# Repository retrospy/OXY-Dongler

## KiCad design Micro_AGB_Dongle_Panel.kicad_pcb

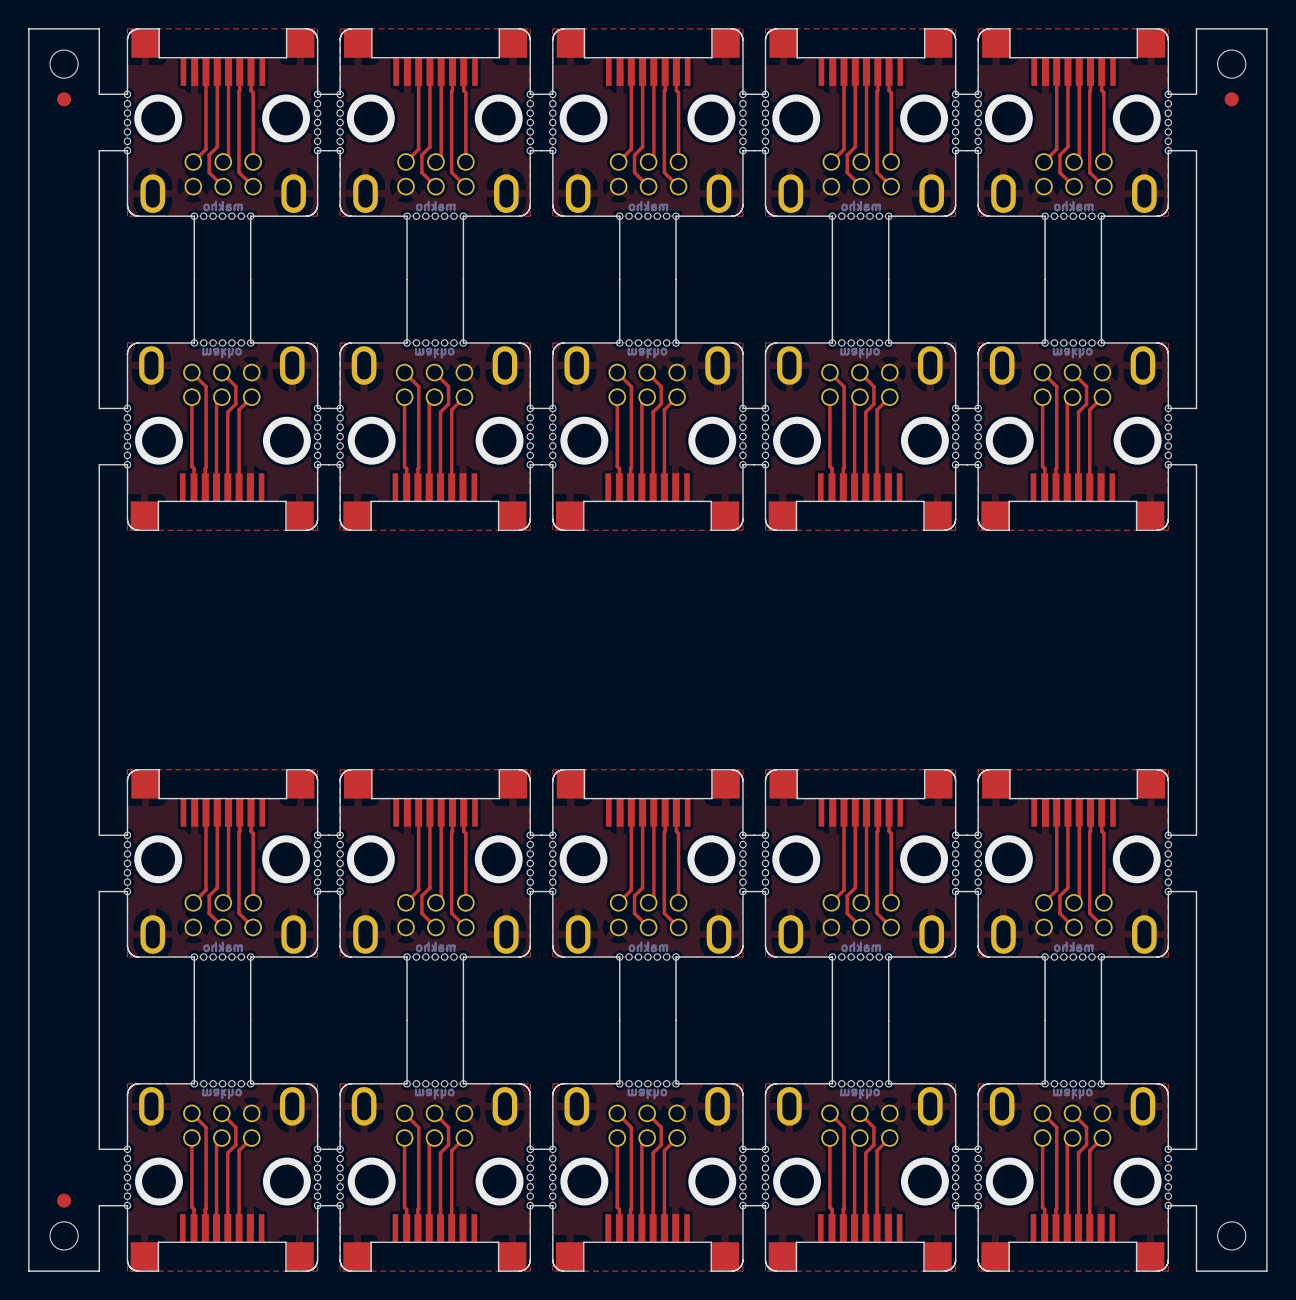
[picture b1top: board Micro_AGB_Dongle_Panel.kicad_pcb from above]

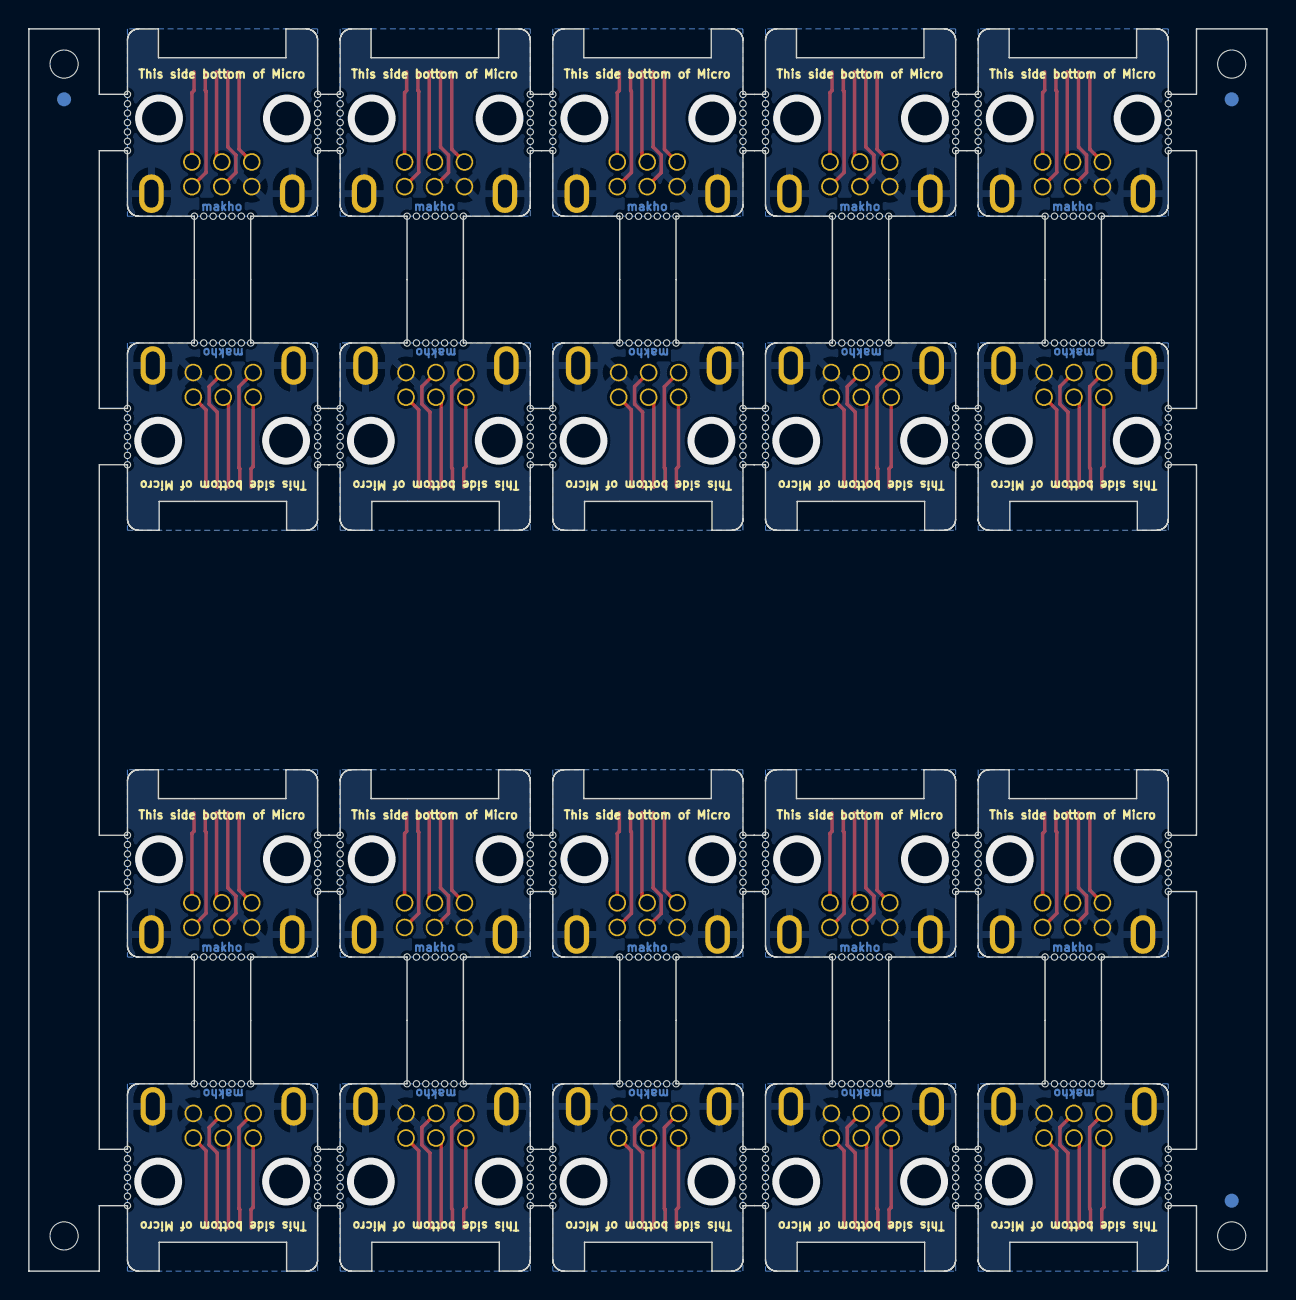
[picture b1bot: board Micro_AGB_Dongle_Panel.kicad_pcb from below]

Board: 2 copper layers, 87.9 x 88.2 mm, 470 parts (3 on the bottom side), 120 nets.

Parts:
EXP1, EXP1#2, EXP1#3, EXP1#4, EXP1#5, EXP1#6, EXP1#7, EXP1#8, EXP1#9, EXP1#10, EXP1#11, EXP1#12, EXP1#13, EXP1#14, EXP1#15, EXP1#16, EXP1#17, EXP1#18, EXP1#19, EXP1#20: OXY_EXP
EXP2, EXP2#2, EXP2#3, EXP2#4, EXP2#5, EXP2#6, EXP2#7, EXP2#8, EXP2#9, EXP2#10, EXP2#11, EXP2#12, EXP2#13, EXP2#14, EXP2#15, EXP2#16, EXP2#17, EXP2#18, EXP2#19, EXP2#20: AGB_EXP
KiKit_FID_B_1, KiKit_FID_B_2, KiKit_FID_B_3: Fiducial
KiKit_FID_T_1, KiKit_FID_T_2, KiKit_FID_T_3: Fiducial
KiKit_MB_1_1, KiKit_MB_1_2, KiKit_MB_1_3, KiKit_MB_1_4, KiKit_MB_1_5, KiKit_MB_1_6, KiKit_MB_1_7, KiKit_MB_2_1, KiKit_MB_2_2, KiKit_MB_2_3, KiKit_MB_2_4, KiKit_MB_2_5, KiKit_MB_2_6, KiKit_MB_2_7, KiKit_MB_3_1, KiKit_MB_3_2, KiKit_MB_3_3, KiKit_MB_3_4, KiKit_MB_3_5, KiKit_MB_3_6, KiKit_MB_3_7, KiKit_MB_4_1, KiKit_MB_4_2, KiKit_MB_4_3, KiKit_MB_4_4, KiKit_MB_4_5, KiKit_MB_4_6, KiKit_MB_4_7, KiKit_MB_5_1, KiKit_MB_5_2, KiKit_MB_5_3, KiKit_MB_5_4, KiKit_MB_5_5, KiKit_MB_5_6, KiKit_MB_5_7, KiKit_MB_6_1, KiKit_MB_6_2, KiKit_MB_6_3, KiKit_MB_6_4, KiKit_MB_6_5, KiKit_MB_6_6, KiKit_MB_6_7, KiKit_MB_7_1, KiKit_MB_7_2, KiKit_MB_7_3, KiKit_MB_7_4, KiKit_MB_7_5, KiKit_MB_7_6, KiKit_MB_7_7, KiKit_MB_8_1, KiKit_MB_8_2, KiKit_MB_8_3, KiKit_MB_8_4, KiKit_MB_8_5, KiKit_MB_8_6, KiKit_MB_8_7, KiKit_MB_9_1, KiKit_MB_9_2, KiKit_MB_9_3, KiKit_MB_9_4, KiKit_MB_9_5, KiKit_MB_9_6, KiKit_MB_9_7, KiKit_MB_10_1, KiKit_MB_10_2, KiKit_MB_10_3, KiKit_MB_10_4, KiKit_MB_10_5, KiKit_MB_10_6, KiKit_MB_10_7, KiKit_MB_11_1, KiKit_MB_11_2, KiKit_MB_11_3, KiKit_MB_11_4, KiKit_MB_11_5, KiKit_MB_11_6, KiKit_MB_11_7, KiKit_MB_12_1, KiKit_MB_12_2, KiKit_MB_12_3, KiKit_MB_12_4, KiKit_MB_12_5, KiKit_MB_12_6, KiKit_MB_12_7, KiKit_MB_13_1, KiKit_MB_13_2, KiKit_MB_13_3, KiKit_MB_13_4, KiKit_MB_13_5, KiKit_MB_13_6, KiKit_MB_13_7, KiKit_MB_14_1, KiKit_MB_14_2, KiKit_MB_14_3, KiKit_MB_14_4, KiKit_MB_14_5, KiKit_MB_14_6, KiKit_MB_14_7, KiKit_MB_15_1, KiKit_MB_15_2, KiKit_MB_15_3, KiKit_MB_15_4, KiKit_MB_15_5, KiKit_MB_15_6, KiKit_MB_15_7, KiKit_MB_16_1, KiKit_MB_16_2, KiKit_MB_16_3, KiKit_MB_16_4, KiKit_MB_16_5, KiKit_MB_16_6, KiKit_MB_16_7, KiKit_MB_17_1, KiKit_MB_17_2, KiKit_MB_17_3, KiKit_MB_17_4, KiKit_MB_17_5, KiKit_MB_17_6, KiKit_MB_17_7, KiKit_MB_18_1, KiKit_MB_18_2, KiKit_MB_18_3, KiKit_MB_18_4, KiKit_MB_18_5, KiKit_MB_18_6, KiKit_MB_18_7, KiKit_MB_20_1, KiKit_MB_20_2, KiKit_MB_20_3, KiKit_MB_20_4, KiKit_MB_20_5, KiKit_MB_20_6, KiKit_MB_20_7, KiKit_MB_21_1, KiKit_MB_21_2, KiKit_MB_21_3, KiKit_MB_21_4, KiKit_MB_21_5, KiKit_MB_21_6, KiKit_MB_21_7, KiKit_MB_22_1, KiKit_MB_22_2, KiKit_MB_22_3, KiKit_MB_22_4, KiKit_MB_22_5, KiKit_MB_22_6, KiKit_MB_22_7, KiKit_MB_24_1, KiKit_MB_24_2, KiKit_MB_24_3, KiKit_MB_24_4, KiKit_MB_24_5, KiKit_MB_24_6, KiKit_MB_24_7, KiKit_MB_25_1, KiKit_MB_25_2, KiKit_MB_25_3, KiKit_MB_25_4, KiKit_MB_25_5, KiKit_MB_25_6, KiKit_MB_25_7, KiKit_MB_26_1, KiKit_MB_26_2, KiKit_MB_26_3, KiKit_MB_26_4, KiKit_MB_26_5, KiKit_MB_26_6, KiKit_MB_26_7, KiKit_MB_28_1, KiKit_MB_28_2, KiKit_MB_28_3, KiKit_MB_28_4, KiKit_MB_28_5, KiKit_MB_28_6, KiKit_MB_28_7, KiKit_MB_29_1, KiKit_MB_29_2, KiKit_MB_29_3, KiKit_MB_29_4, KiKit_MB_29_5, KiKit_MB_29_6, KiKit_MB_29_7, KiKit_MB_30_1, KiKit_MB_30_2, KiKit_MB_30_3, KiKit_MB_30_4, KiKit_MB_30_5, KiKit_MB_30_6, KiKit_MB_30_7, KiKit_MB_32_1, KiKit_MB_32_2, KiKit_MB_32_3, KiKit_MB_32_4, KiKit_MB_32_5, KiKit_MB_32_6, KiKit_MB_32_7, KiKit_MB_33_1, KiKit_MB_33_2, KiKit_MB_33_3, KiKit_MB_33_4, KiKit_MB_33_5, KiKit_MB_33_6, KiKit_MB_33_7, KiKit_MB_34_1, KiKit_MB_34_2, KiKit_MB_34_3, KiKit_MB_34_4, KiKit_MB_34_5, KiKit_MB_34_6, KiKit_MB_34_7, KiKit_MB_36_1, KiKit_MB_36_2, KiKit_MB_36_3, KiKit_MB_36_4, KiKit_MB_36_5, KiKit_MB_36_6, KiKit_MB_36_7, KiKit_MB_37_1, KiKit_MB_37_2, KiKit_MB_37_3, KiKit_MB_37_4, KiKit_MB_37_5, KiKit_MB_37_6, KiKit_MB_37_7, KiKit_MB_39_1, KiKit_MB_39_2, KiKit_MB_39_3, KiKit_MB_39_4, KiKit_MB_39_5, KiKit_MB_39_6, KiKit_MB_39_7, KiKit_MB_40_1, KiKit_MB_40_2, KiKit_MB_40_3, KiKit_MB_40_4, KiKit_MB_40_5, KiKit_MB_40_6, KiKit_MB_40_7, KiKit_MB_41_1, KiKit_MB_41_2, KiKit_MB_41_3, KiKit_MB_41_4, KiKit_MB_41_5, KiKit_MB_41_6, KiKit_MB_41_7, KiKit_MB_43_1, KiKit_MB_43_2, KiKit_MB_43_3, KiKit_MB_43_4, KiKit_MB_43_5, KiKit_MB_43_6, KiKit_MB_43_7, KiKit_MB_44_1, KiKit_MB_44_2, KiKit_MB_44_3, KiKit_MB_44_4, KiKit_MB_44_5, KiKit_MB_44_6, KiKit_MB_44_7, KiKit_MB_45_1, KiKit_MB_45_2, KiKit_MB_45_3, KiKit_MB_45_4, KiKit_MB_45_5, KiKit_MB_45_6, KiKit_MB_45_7, KiKit_MB_47_1, KiKit_MB_47_2, KiKit_MB_47_3, KiKit_MB_47_4, KiKit_MB_47_5, KiKit_MB_47_6, KiKit_MB_47_7, KiKit_MB_48_1, KiKit_MB_48_2, KiKit_MB_48_3, KiKit_MB_48_4, KiKit_MB_48_5, KiKit_MB_48_6, KiKit_MB_48_7, KiKit_MB_49_1, KiKit_MB_49_2, KiKit_MB_49_3, KiKit_MB_49_4, KiKit_MB_49_5, KiKit_MB_49_6, KiKit_MB_49_7, KiKit_MB_51_1, KiKit_MB_51_2, KiKit_MB_51_3, KiKit_MB_51_4, KiKit_MB_51_5, KiKit_MB_51_6, KiKit_MB_51_7, KiKit_MB_52_1, KiKit_MB_52_2, KiKit_MB_52_3, KiKit_MB_52_4, KiKit_MB_52_5, KiKit_MB_52_6, KiKit_MB_52_7, KiKit_MB_53_1, KiKit_MB_53_2, KiKit_MB_53_3, KiKit_MB_53_4, KiKit_MB_53_5, KiKit_MB_53_6, KiKit_MB_53_7, KiKit_MB_55_1, KiKit_MB_55_2, KiKit_MB_55_3, KiKit_MB_55_4, KiKit_MB_55_5, KiKit_MB_55_6, KiKit_MB_55_7, KiKit_MB_56_1, KiKit_MB_56_2, KiKit_MB_56_3, KiKit_MB_56_4, KiKit_MB_56_5, KiKit_MB_56_6, KiKit_MB_56_7, KiKit_MB_57_1, KiKit_MB_57_2, KiKit_MB_57_3, KiKit_MB_57_4, KiKit_MB_57_5, KiKit_MB_57_6, KiKit_MB_57_7, KiKit_MB_58_1, KiKit_MB_58_2, KiKit_MB_58_3, KiKit_MB_58_4, KiKit_MB_58_5, KiKit_MB_58_6, KiKit_MB_58_7, KiKit_MB_59_1, KiKit_MB_59_2, KiKit_MB_59_3, KiKit_MB_59_4, KiKit_MB_59_5, KiKit_MB_59_6, KiKit_MB_59_7, KiKit_MB_60_1, KiKit_MB_60_2, KiKit_MB_60_3, KiKit_MB_60_4, KiKit_MB_60_5, KiKit_MB_60_6, KiKit_MB_60_7, KiKit_MB_61_1, KiKit_MB_61_2, KiKit_MB_61_3, KiKit_MB_61_4, KiKit_MB_61_5, KiKit_MB_61_6, KiKit_MB_61_7, KiKit_MB_62_1, KiKit_MB_62_2, KiKit_MB_62_3, KiKit_MB_62_4, KiKit_MB_62_5, KiKit_MB_62_6, KiKit_MB_62_7, KiKit_MB_63_1, KiKit_MB_63_2, KiKit_MB_63_3, KiKit_MB_63_4, KiKit_MB_63_5, KiKit_MB_63_6, KiKit_MB_63_7, KiKit_MB_64_1, KiKit_MB_64_2, KiKit_MB_64_3, KiKit_MB_64_4, KiKit_MB_64_5, KiKit_MB_64_6, KiKit_MB_64_7, KiKit_MB_65_1, KiKit_MB_65_2, KiKit_MB_65_3, KiKit_MB_65_4, KiKit_MB_65_5, KiKit_MB_65_6, KiKit_MB_65_7, KiKit_MB_66_1, KiKit_MB_66_2, KiKit_MB_66_3, KiKit_MB_66_4, KiKit_MB_66_5, KiKit_MB_66_6, KiKit_MB_66_7, KiKit_MB_67_1, KiKit_MB_67_2, KiKit_MB_67_3, KiKit_MB_67_4, KiKit_MB_67_5, KiKit_MB_67_6, KiKit_MB_67_7, KiKit_MB_68_1, KiKit_MB_68_2, KiKit_MB_68_3, KiKit_MB_68_4, KiKit_MB_68_5, KiKit_MB_68_6, KiKit_MB_68_7, KiKit_MB_69_1, KiKit_MB_69_2, KiKit_MB_69_3, KiKit_MB_69_4, KiKit_MB_69_5, KiKit_MB_69_6, KiKit_MB_69_7, KiKit_MB_70_1, KiKit_MB_70_2, KiKit_MB_70_3, KiKit_MB_70_4, KiKit_MB_70_5, KiKit_MB_70_6, KiKit_MB_70_7: NPTH
KiKit_TO_1, KiKit_TO_2, KiKit_TO_3, KiKit_TO_4: NPTH

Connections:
Board_0-Net-(EXP1-GND): EXP1#2.6 (GND), EXP2#5.6 (GND)
Board_0-Net-(EXP1-PWR): EXP1#2.1 (PWR), EXP2#5.1 (PWR)
Board_0-Net-(EXP1-SC): EXP1#2.5 (SC), EXP2#5.5 (SC)
Board_0-Net-(EXP1-SD): EXP1#2.4 (SD), EXP2#5.4 (SD)
Board_0-Net-(EXP1-SI): EXP1#2.3 (SI), EXP2#5.3 (SI)
Board_0-Net-(EXP1-SO): EXP1#2.2 (SO), EXP2#5.2 (SO)
Board_1-Net-(EXP1-GND): EXP1#19.6 (GND), EXP2#15.6 (GND)
Board_1-Net-(EXP1-PWR): EXP1#19.1 (PWR), EXP2#15.1 (PWR)
Board_1-Net-(EXP1-SC): EXP1#19.5 (SC), EXP2#15.5 (SC)
Board_1-Net-(EXP1-SD): EXP1#19.4 (SD), EXP2#15.4 (SD)
Board_1-Net-(EXP1-SI): EXP1#19.3 (SI), EXP2#15.3 (SI)
Board_1-Net-(EXP1-SO): EXP1#19.2 (SO), EXP2#15.2 (SO)
Board_2-Net-(EXP1-GND): EXP1#20.6 (GND), EXP2#2.6 (GND)
Board_2-Net-(EXP1-PWR): EXP1#20.1 (PWR), EXP2#2.1 (PWR)
Board_2-Net-(EXP1-SC): EXP1#20.5 (SC), EXP2#2.5 (SC)
Board_2-Net-(EXP1-SD): EXP1#20.4 (SD), EXP2#2.4 (SD)
Board_2-Net-(EXP1-SI): EXP1#20.3 (SI), EXP2#2.3 (SI)
Board_2-Net-(EXP1-SO): EXP1#20.2 (SO), EXP2#2.2 (SO)
Board_3-Net-(EXP1-GND): EXP1#7.6 (GND), EXP2#16.6 (GND)
Board_3-Net-(EXP1-PWR): EXP1#7.1 (PWR), EXP2#16.1 (PWR)
Board_3-Net-(EXP1-SC): EXP1#7.5 (SC), EXP2#16.5 (SC)
Board_3-Net-(EXP1-SD): EXP1#7.4 (SD), EXP2#16.4 (SD)
Board_3-Net-(EXP1-SI): EXP1#7.3 (SI), EXP2#16.3 (SI)
Board_3-Net-(EXP1-SO): EXP1#7.2 (SO), EXP2#16.2 (SO)
Board_4-Net-(EXP1-GND): EXP1#12.6 (GND), EXP2#17.6 (GND)
Board_4-Net-(EXP1-PWR): EXP1#12.1 (PWR), EXP2#17.1 (PWR)
Board_4-Net-(EXP1-SC): EXP1#12.5 (SC), EXP2#17.5 (SC)
Board_4-Net-(EXP1-SD): EXP1#12.4 (SD), EXP2#17.4 (SD)
Board_4-Net-(EXP1-SI): EXP1#12.3 (SI), EXP2#17.3 (SI)
Board_4-Net-(EXP1-SO): EXP1#12.2 (SO), EXP2#17.2 (SO)
Board_5-Net-(EXP1-GND): EXP1#13.6 (GND), EXP2#14.6 (GND)
Board_5-Net-(EXP1-PWR): EXP1#13.1 (PWR), EXP2#14.1 (PWR)
Board_5-Net-(EXP1-SC): EXP1#13.5 (SC), EXP2#14.5 (SC)
Board_5-Net-(EXP1-SD): EXP1#13.4 (SD), EXP2#14.4 (SD)
Board_5-Net-(EXP1-SI): EXP1#13.3 (SI), EXP2#14.3 (SI)
Board_5-Net-(EXP1-SO): EXP1#13.2 (SO), EXP2#14.2 (SO)
Board_6-Net-(EXP1-GND): EXP1#15.6 (GND), EXP2#11.6 (GND)
Board_6-Net-(EXP1-PWR): EXP1#15.1 (PWR), EXP2#11.1 (PWR)
Board_6-Net-(EXP1-SC): EXP1#15.5 (SC), EXP2#11.5 (SC)
Board_6-Net-(EXP1-SD): EXP1#15.4 (SD), EXP2#11.4 (SD)
Board_6-Net-(EXP1-SI): EXP1#15.3 (SI), EXP2#11.3 (SI)
Board_6-Net-(EXP1-SO): EXP1#15.2 (SO), EXP2#11.2 (SO)
Board_7-Net-(EXP1-GND): EXP1#3.6 (GND), EXP2.6 (GND)
Board_7-Net-(EXP1-PWR): EXP1#3.1 (PWR), EXP2.1 (PWR)
Board_7-Net-(EXP1-SC): EXP1#3.5 (SC), EXP2.5 (SC)
Board_7-Net-(EXP1-SD): EXP1#3.4 (SD), EXP2.4 (SD)
Board_7-Net-(EXP1-SI): EXP1#3.3 (SI), EXP2.3 (SI)
Board_7-Net-(EXP1-SO): EXP1#3.2 (SO), EXP2.2 (SO)
Board_8-Net-(EXP1-GND): EXP1#8.6 (GND), EXP2#12.6 (GND)
Board_8-Net-(EXP1-PWR): EXP1#8.1 (PWR), EXP2#12.1 (PWR)
Board_8-Net-(EXP1-SC): EXP1#8.5 (SC), EXP2#12.5 (SC)
Board_8-Net-(EXP1-SD): EXP1#8.4 (SD), EXP2#12.4 (SD)
Board_8-Net-(EXP1-SI): EXP1#8.3 (SI), EXP2#12.3 (SI)
Board_8-Net-(EXP1-SO): EXP1#8.2 (SO), EXP2#12.2 (SO)
Board_9-Net-(EXP1-GND): EXP1#18.6 (GND), EXP2#7.6 (GND)
Board_9-Net-(EXP1-PWR): EXP1#18.1 (PWR), EXP2#7.1 (PWR)
Board_9-Net-(EXP1-SC): EXP1#18.5 (SC), EXP2#7.5 (SC)
Board_9-Net-(EXP1-SD): EXP1#18.4 (SD), EXP2#7.4 (SD)
Board_9-Net-(EXP1-SI): EXP1#18.3 (SI), EXP2#7.3 (SI)
Board_9-Net-(EXP1-SO): EXP1#18.2 (SO), EXP2#7.2 (SO)
Board_10-Net-(EXP1-GND): EXP1#14.6 (GND), EXP2#3.6 (GND)
Board_10-Net-(EXP1-PWR): EXP1#14.1 (PWR), EXP2#3.1 (PWR)
Board_10-Net-(EXP1-SC): EXP1#14.5 (SC), EXP2#3.5 (SC)
Board_10-Net-(EXP1-SD): EXP1#14.4 (SD), EXP2#3.4 (SD)
Board_10-Net-(EXP1-SI): EXP1#14.3 (SI), EXP2#3.3 (SI)
Board_10-Net-(EXP1-SO): EXP1#14.2 (SO), EXP2#3.2 (SO)
Board_11-Net-(EXP1-GND): EXP1.6 (GND), EXP2#20.6 (GND)
Board_11-Net-(EXP1-PWR): EXP1.1 (PWR), EXP2#20.1 (PWR)
Board_11-Net-(EXP1-SC): EXP1.5 (SC), EXP2#20.5 (SC)
Board_11-Net-(EXP1-SD): EXP1.4 (SD), EXP2#20.4 (SD)
Board_11-Net-(EXP1-SI): EXP1.3 (SI), EXP2#20.3 (SI)
Board_11-Net-(EXP1-SO): EXP1.2 (SO), EXP2#20.2 (SO)
Board_12-Net-(EXP1-GND): EXP1#6.6 (GND), EXP2#9.6 (GND)
Board_12-Net-(EXP1-PWR): EXP1#6.1 (PWR), EXP2#9.1 (PWR)
Board_12-Net-(EXP1-SC): EXP1#6.5 (SC), EXP2#9.5 (SC)
Board_12-Net-(EXP1-SD): EXP1#6.4 (SD), EXP2#9.4 (SD)
Board_12-Net-(EXP1-SI): EXP1#6.3 (SI), EXP2#9.3 (SI)
Board_12-Net-(EXP1-SO): EXP1#6.2 (SO), EXP2#9.2 (SO)
Board_13-Net-(EXP1-GND): EXP1#9.6 (GND), EXP2#10.6 (GND)
Board_13-Net-(EXP1-PWR): EXP1#9.1 (PWR), EXP2#10.1 (PWR)
Board_13-Net-(EXP1-SC): EXP1#9.5 (SC), EXP2#10.5 (SC)
Board_13-Net-(EXP1-SD): EXP1#9.4 (SD), EXP2#10.4 (SD)
Board_13-Net-(EXP1-SI): EXP1#9.3 (SI), EXP2#10.3 (SI)
Board_13-Net-(EXP1-SO): EXP1#9.2 (SO), EXP2#10.2 (SO)
Board_14-Net-(EXP1-GND): EXP1#5.6 (GND), EXP2#4.6 (GND)
Board_14-Net-(EXP1-PWR): EXP1#5.1 (PWR), EXP2#4.1 (PWR)
Board_14-Net-(EXP1-SC): EXP1#5.5 (SC), EXP2#4.5 (SC)
Board_14-Net-(EXP1-SD): EXP1#5.4 (SD), EXP2#4.4 (SD)
Board_14-Net-(EXP1-SI): EXP1#5.3 (SI), EXP2#4.3 (SI)
Board_14-Net-(EXP1-SO): EXP1#5.2 (SO), EXP2#4.2 (SO)
Board_15-Net-(EXP1-GND): EXP1#16.6 (GND), EXP2#18.6 (GND)
Board_15-Net-(EXP1-PWR): EXP1#16.1 (PWR), EXP2#18.1 (PWR)
Board_15-Net-(EXP1-SC): EXP1#16.5 (SC), EXP2#18.5 (SC)
Board_15-Net-(EXP1-SD): EXP1#16.4 (SD), EXP2#18.4 (SD)
Board_15-Net-(EXP1-SI): EXP1#16.3 (SI), EXP2#18.3 (SI)
Board_15-Net-(EXP1-SO): EXP1#16.2 (SO), EXP2#18.2 (SO)
Board_16-Net-(EXP1-GND): EXP1#4.6 (GND), EXP2#13.6 (GND)
Board_16-Net-(EXP1-PWR): EXP1#4.1 (PWR), EXP2#13.1 (PWR)
Board_16-Net-(EXP1-SC): EXP1#4.5 (SC), EXP2#13.5 (SC)
Board_16-Net-(EXP1-SD): EXP1#4.4 (SD), EXP2#13.4 (SD)
Board_16-Net-(EXP1-SI): EXP1#4.3 (SI), EXP2#13.3 (SI)
Board_16-Net-(EXP1-SO): EXP1#4.2 (SO), EXP2#13.2 (SO)
Board_17-Net-(EXP1-GND): EXP1#11.6 (GND), EXP2#8.6 (GND)
Board_17-Net-(EXP1-PWR): EXP1#11.1 (PWR), EXP2#8.1 (PWR)
Board_17-Net-(EXP1-SC): EXP1#11.5 (SC), EXP2#8.5 (SC)
Board_17-Net-(EXP1-SD): EXP1#11.4 (SD), EXP2#8.4 (SD)
Board_17-Net-(EXP1-SI): EXP1#11.3 (SI), EXP2#8.3 (SI)
Board_17-Net-(EXP1-SO): EXP1#11.2 (SO), EXP2#8.2 (SO)
Board_18-Net-(EXP1-GND): EXP1#10.6 (GND), EXP2#6.6 (GND)
Board_18-Net-(EXP1-PWR): EXP1#10.1 (PWR), EXP2#6.1 (PWR)
Board_18-Net-(EXP1-SC): EXP1#10.5 (SC), EXP2#6.5 (SC)
Board_18-Net-(EXP1-SD): EXP1#10.4 (SD), EXP2#6.4 (SD)
Board_18-Net-(EXP1-SI): EXP1#10.3 (SI), EXP2#6.3 (SI)
Board_18-Net-(EXP1-SO): EXP1#10.2 (SO), EXP2#6.2 (SO)
Board_19-Net-(EXP1-GND): EXP1#17.6 (GND), EXP2#19.6 (GND)
Board_19-Net-(EXP1-PWR): EXP1#17.1 (PWR), EXP2#19.1 (PWR)
Board_19-Net-(EXP1-SC): EXP1#17.5 (SC), EXP2#19.5 (SC)
Board_19-Net-(EXP1-SD): EXP1#17.4 (SD), EXP2#19.4 (SD)
Board_19-Net-(EXP1-SI): EXP1#17.3 (SI), EXP2#19.3 (SI)
Board_19-Net-(EXP1-SO): EXP1#17.2 (SO), EXP2#19.2 (SO)

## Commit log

2023-12-22 Added M2 bolt holes & removed charging pins
2023-12-24 Added panel
